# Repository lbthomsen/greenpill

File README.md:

# greenpill
STM32 Green Pill

https://stm32world.com/wiki/Green_Pill

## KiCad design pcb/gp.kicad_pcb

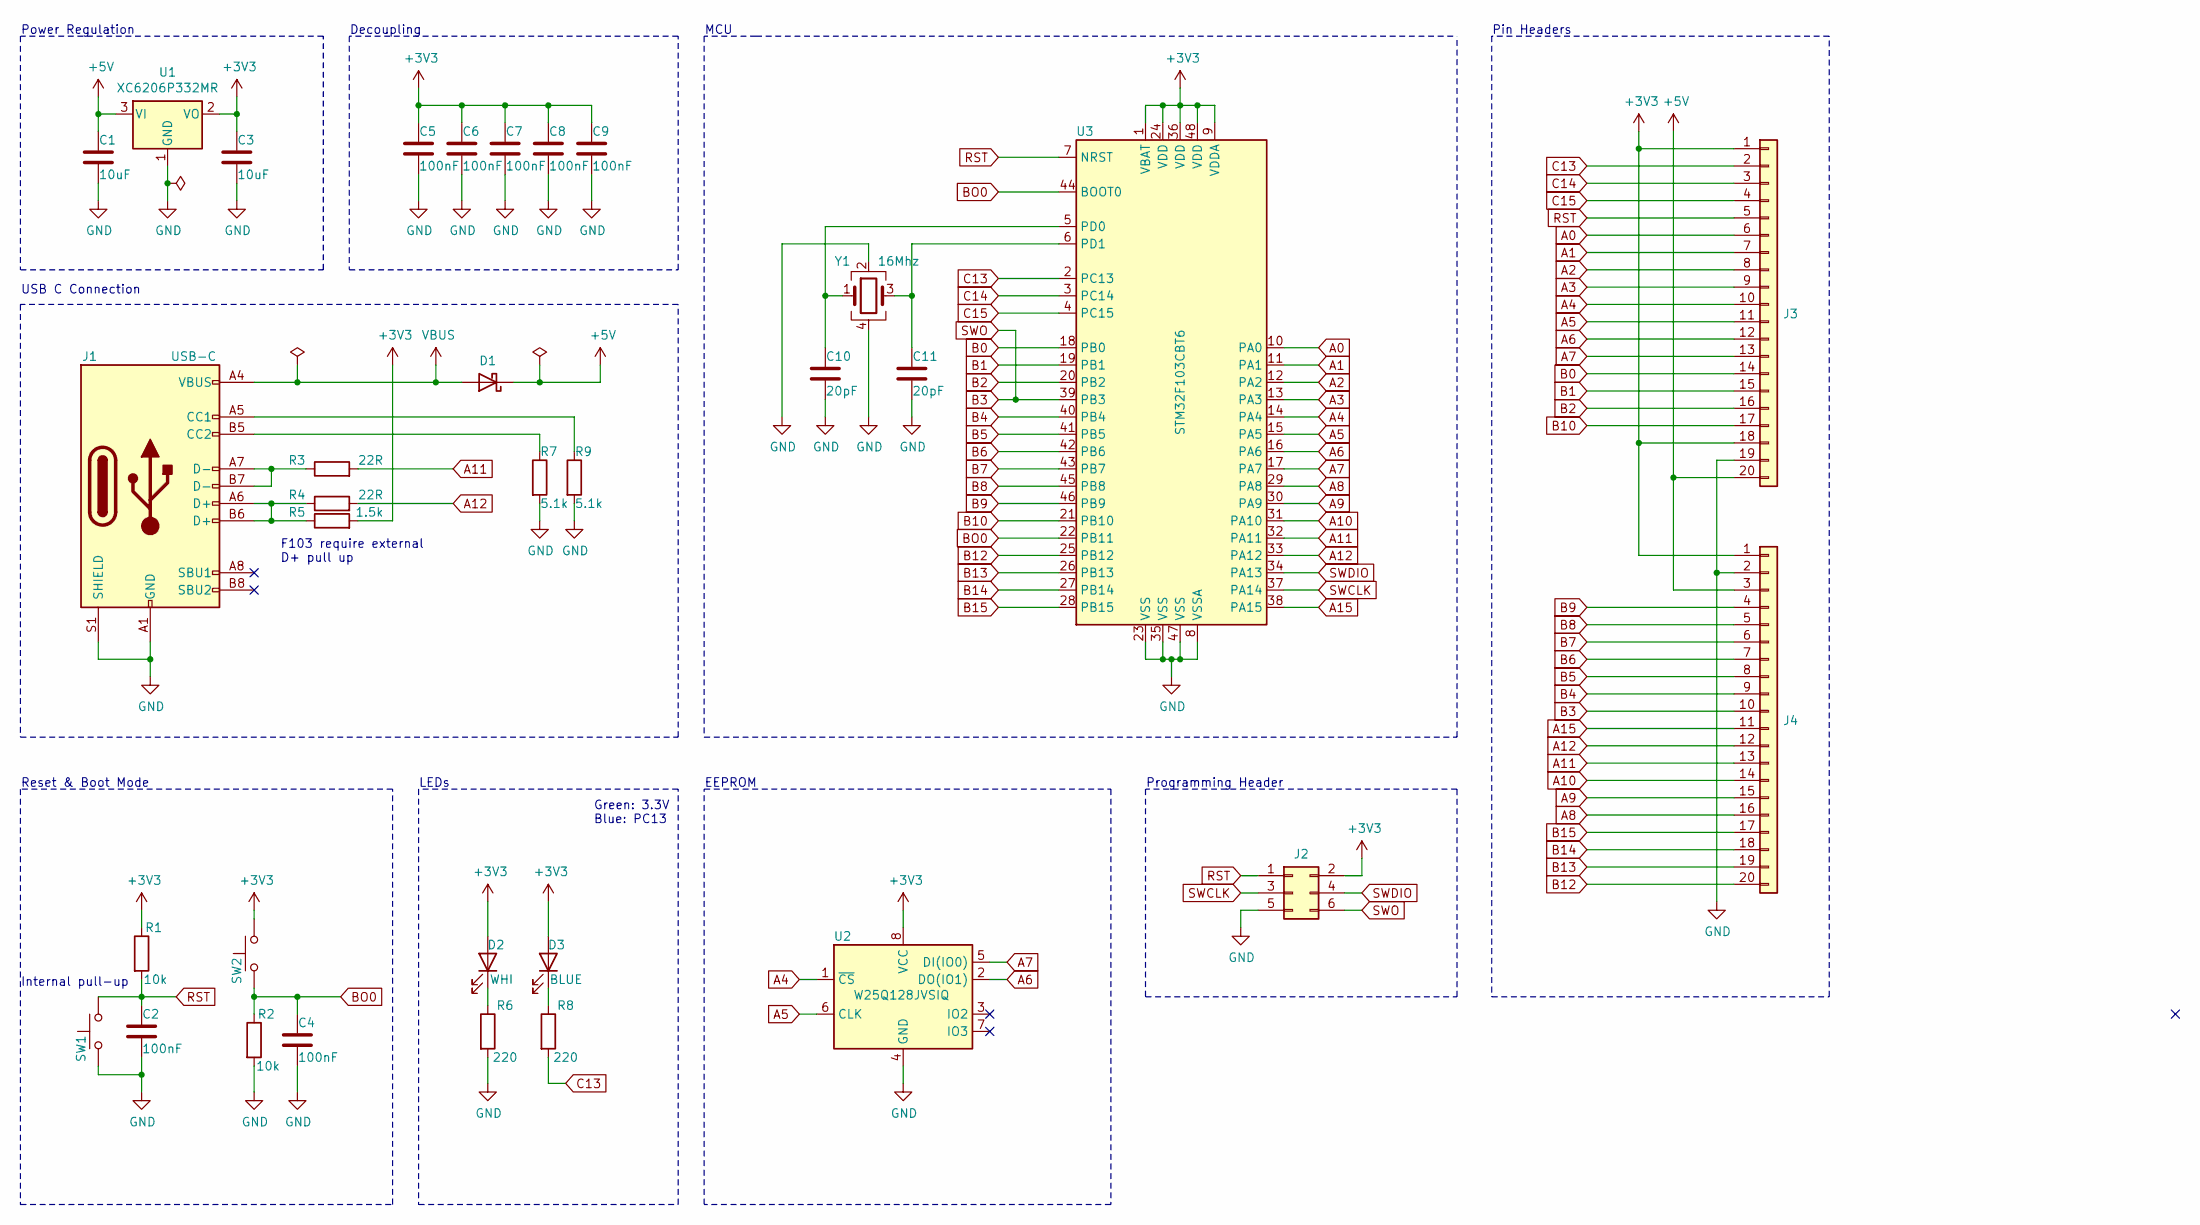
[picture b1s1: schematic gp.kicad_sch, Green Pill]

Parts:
C1, C3: 10uF; C_0603_1608Metric; LCSC C19702
C2, C4, C5, C6, C7, C8, C9: 100nF; C_0402_1005Metric; LCSC C1525
C10, C11: 20pF; C_0402_1005Metric; LCSC C1554
D1: D_SOD-123; LCSC C8598
D2: WHI; LED_0603_1608Metric; LCSC C2290
D3: BLUE; LED_0603_1608Metric; LCSC C2288
J1: USB-C; USB_C_Receptacle_HRO_TYPE-C-31-M-12; LCSC C165948
J2: PinHeader_2x03_P2.54mm_Horizontal
J3, J4: PinHeader_1x20_P2.54mm_Vertical
R1, R2: 10k; R_0402_1005Metric; LCSC C25744
R3, R4: 22R; R_0402_1005Metric; LCSC C25092
R5: 1.5k; R_0402_1005Metric; LCSC C25867
R6, R8: 220; R_0402_1005Metric; LCSC C25091
R7, R9: 5.1k; R_0402_1005Metric; LCSC C25905
SW1, SW2: TS-1088R-02526; LCSC C455281
U1: XC6206P332MR; SOT-23; LCSC C5446
U2: W25Q128JVSIQ; SOIC-8_5.3x5.3mm_P1.27mm; LCSC C97521
U3: STM32F103CBT6; LQFP-48_7x7mm_P0.5mm; LCSC C8304
Y1: 16Mhz; Crystal_SMD_3225-4Pin_3.2x2.5mm; LCSC C13738

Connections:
+3V3: C3.1, C5.1, C6.1, C7.1, C8.1, C9.1, D2.2 (A), D3.2 (A), J2.2, J3.1, J3.18, J4.1, R1.1, R5.2, SW2.2, U1.2 (VO), U2.8 (VCC), U3.1 (VBAT), U3.9 (VDDA), U3.24 (VDD), U3.36 (VDD), U3.48 (VDD)
+5V: C1.1, D1.1 (K), J3.20, J4.3, U1.3 (VI)
A0: J3.6, U3.10 (PA0)
A1: J3.7, U3.11 (PA1)
A2: J3.8, U3.12 (PA2)
A3: J3.9, U3.13 (PA3)
A4: J3.10, U2.1 (~CS), U3.14 (PA4)
A5: J3.11, U2.6 (CLK), U3.15 (PA5)
A6: J3.12, U2.2 (DO(IO1)), U3.16 (PA6)
A7: J3.13, U2.5 (DI(IO0)), U3.17 (PA7)
A8: J4.16, U3.29 (PA8)
A9: J4.15, U3.30 (PA9)
A10: J4.14, U3.31 (PA10)
A11: J4.13, R3.2, U3.32 (PA11)
A12: J4.12, R4.2, U3.33 (PA12)
A15: J4.11, U3.38 (PA15)
B0: J3.14, U3.18 (PB0)
B1: J3.15, U3.19 (PB1)
B2: J3.16, U3.20 (PB2)
B3: J2.6, J4.10, U3.39 (PB3)
B4: J4.9, U3.40 (PB4)
B5: J4.8, U3.41 (PB5)
B6: J4.7, U3.42 (PB6)
B7: J4.6, U3.43 (PB7)
B8: J4.5, U3.45 (PB8)
B9: J4.4, U3.46 (PB9)
B10: J3.17, U3.21 (PB10)
B12: J4.20, U3.25 (PB12)
B13: J4.19, U3.26 (PB13)
B14: J4.18, U3.27 (PB14)
B15: J4.17, U3.28 (PB15)
BO0: C4.1, R2.1, SW2.1, U3.22 (PB11), U3.44 (BOOT0)
C13: J3.2, R8.2, U3.2 (PC13)
C14: J3.3, U3.3 (PC14)
C15: J3.4, U3.4 (PC15)
GND: C1.2, C2.2, C3.2, C4.2, C5.2, C6.2, C7.2, C8.2, C9.2, C10.2, C11.2, J1.A1 (GND), J1.A12 (GND), J1.B1 (GND), J1.B12 (GND), J1.S1 (SHIELD), J2.5, J3.19, J4.2, R2.2, R6.2, R7.2, R9.2, SW1.1, U1.1 (GND), U2.4 (GND), U3.8 (VSSA), U3.23 (VSS), U3.35 (VSS), U3.47 (VSS), Y1.2, Y1.4
unnamed: D2.1 (K), R6.1
unnamed: D3.1 (K), R8.1
unnamed: J1.A5 (CC1), R9.1
unnamed: J1.B5 (CC2), R7.1
unnamed: J1.A6 (D+), J1.B6 (D+), R4.1, R5.1
unnamed: J1.A7 (D-), J1.B7 (D-), R3.1
unnamed: C10.1, U3.5 (PD0), Y1.1
unnamed: C11.1, U3.6 (PD1), Y1.3
RST: C2.1, J2.1, J3.5, R1.2, SW1.2, U3.7 (NRST)
SWCLK: J2.3, U3.37 (PA14)
SWDIO: J2.4, U3.34 (PA13)
VBUS: D1.2 (A), J1.A4 (VBUS), J1.A9 (VBUS), J1.B4 (VBUS), J1.B9 (VBUS)

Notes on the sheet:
Decoupling
Green: 3.3V Blue: PC13
MCU
Reset & Boot Mode
USB C Connection
Internal pull-up
Power Regulation
Pin Headers
F103 require external D+ pull up
Programming Header
LEDs
EEPROM

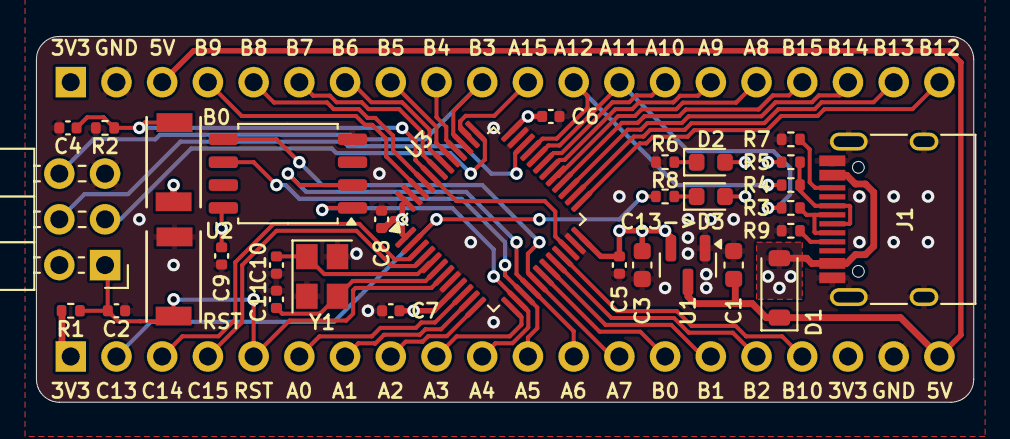
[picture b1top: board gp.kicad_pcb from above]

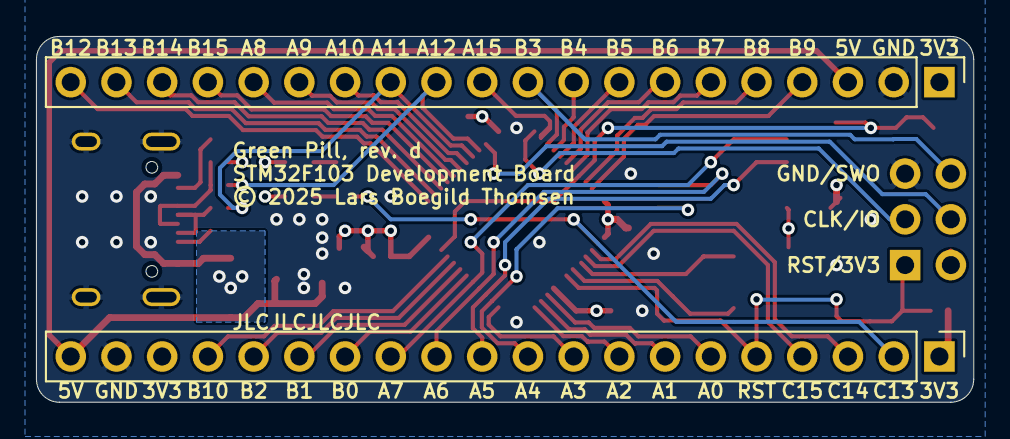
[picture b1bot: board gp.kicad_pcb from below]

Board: 4 copper layers, 52.1 x 20.3 mm, 33 parts (2 on the bottom side), 48 nets.

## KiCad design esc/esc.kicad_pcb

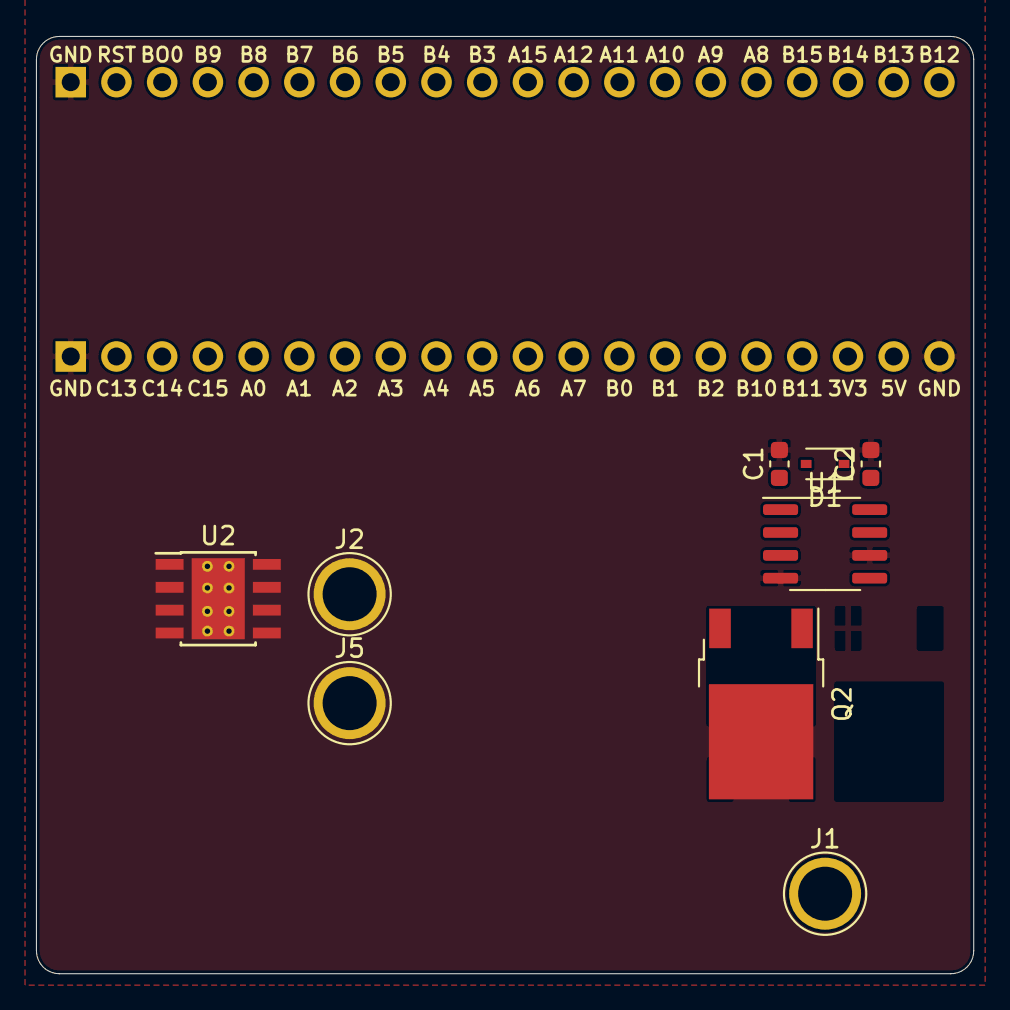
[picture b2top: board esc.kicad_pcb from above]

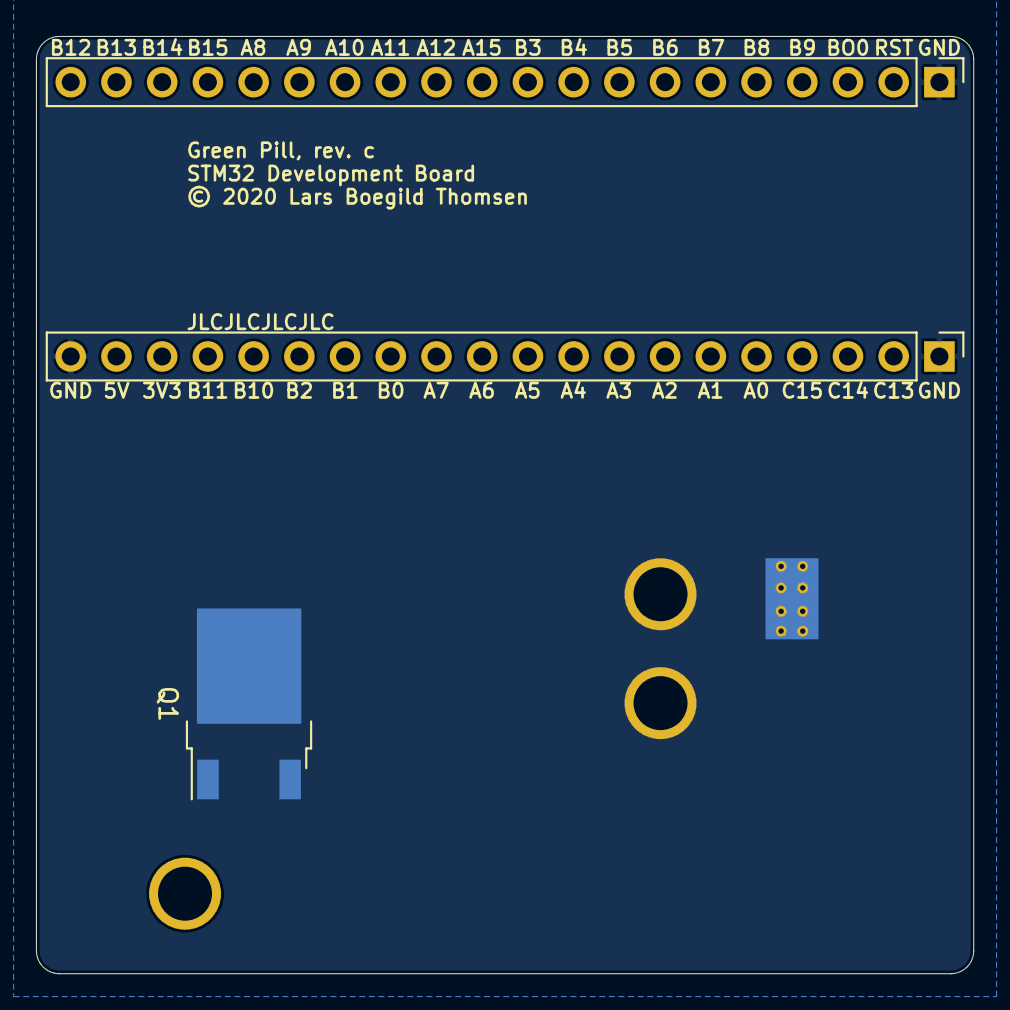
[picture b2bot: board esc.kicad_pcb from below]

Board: 2 copper layers, 52.1 x 52.1 mm, 12 parts (3 on the bottom side), 6 nets, no tracks yet.

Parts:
C1, C2: C; C_0603_1608Metric
D1: D_SOD-323
J1, J2, J5: TestPoint_Plated_Hole_D3.0mm
J3, J4: PinHeader_1x20_P2.54mm_Vertical
Q1, Q2: NCEP60T12AK; TO-252-2
U1: IR2101; SOIC-8_3.9x4.9mm_P1.27mm
U2: TPS5430DDA; TI_SO-PowerPAD-8_ThermalVias

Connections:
+3V3: C1.1, D1.2, J3.18, U1.1
A: J1.1, Q1.3, Q2.2
DAH: Q1.1, U1.7
DAL: Q2.1, U1.5
GND: C1.2, C2.2, J3.1, J3.20, J4.1, J5.1, Q2.3, U1.4, U1.6
VDC: C2.1, D1.1, Q1.2, U1.8

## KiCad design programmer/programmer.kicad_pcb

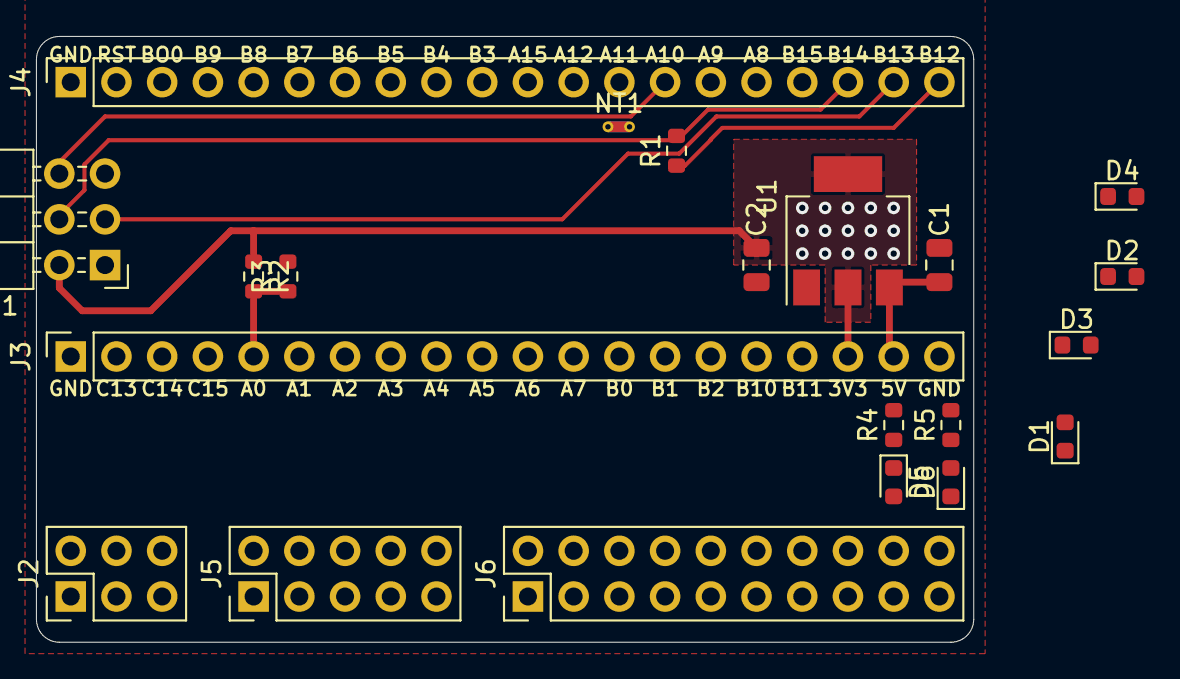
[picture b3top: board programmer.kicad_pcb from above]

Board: 2 copper layers, 52.1 x 33.7 mm, 21 parts (0 on the bottom side), 12 nets.

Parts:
C1, C2: 10uF; C_0805_2012Metric
D1: YL; LED_0603_1608Metric
D2: GR; LED_0603_1608Metric
D3, D6: BL; LED_0603_1608Metric
D4, D5: RD; LED_0603_1608Metric
J1: PinHeader_2x03_P2.54mm_Horizontal
J2: PinHeader_2x03_P2.54mm_Vertical
J3, J4: PinSocket_1x20_P2.54mm_Vertical
J5: PinHeader_2x05_P2.54mm_Vertical
J6: PinHeader_2x10_P2.54mm_Vertical
NT1: NetTie-2_THT_Pad0.3mm
R1: 100; R_0603_1608Metric
R2, R3: 4.7; R_0603_1608Metric
R4, R5: 470; R_0603_1608Metric
U1: AMS1117-3.3; SOT-223-3_TabPin2

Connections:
+3V3: C2.1, D5.2, J1.2, J2.2, J3.18, R2.1, U1.2
+5V: C1.1, J3.19, U1.3
A0: J3.5, R2.2, R3.1
A9: J4.15, R4.2, R5.2
A10: J4.14, NT1.2
B12: J4.20, R1.1
B13: J1.3, J2.3, J4.19
B14: J1.4, J2.4, J4.18, R1.2
GND: C1.2, C2.2, D6.1, J1.5, J2.5, J3.1, J3.20, J4.1, R3.2, U1.1
unnamed: D5.1, R4.1
unnamed: D6.2, R5.1
T_SWO: J1.6, J2.6, NT1.1

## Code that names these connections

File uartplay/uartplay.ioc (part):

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Mcu.Name=STM32F103C(8-B)Tx
Mcu.Package=LQFP48
Mcu.UserName=STM32F103CBTx
PA0-WKUP.GPIOParameters=GPIO_Label
PA0-WKUP.GPIO_Label=DEBUG
PA0-WKUP.Signal=GPIO_Output
PA10.Mode=Asynchronous
PA10.Signal=USART1_RX
PA13.Mode=Serial_Wire
PA13.Signal=SYS_JTMS-SWDIO
PA14.Mode=Serial_Wire
PA14.Signal=SYS_JTCK-SWCLK
PA2.Mode=Asynchronous
PA2.Signal=USART2_TX
PA3.Mode=Asynchronous
PA3.Signal=USART2_RX
PA9.Mode=Asynchronous
PA9.Signal=USART1_TX
PB10.Mode=Asynchronous
PB10.Signal=USART3_TX
PB11.Mode=Asynchronous
PB11.Signal=USART3_RX
PC13-TAMPER-RTC.GPIOParameters=PinState,GPIO_PuPd,GPIO_Label,GPIO_ModeDefaultOutputPP
PC13-TAMPER-RTC.GPIO_Label=LED
PC13-TAMPER-RTC.GPIO_ModeDefaultOutputPP=GPIO_MODE_OUTPUT_OD
PC13-TAMPER-RTC.GPIO_PuPd=GPIO_NOPULL
PC13-TAMPER-RTC.PinState=GPIO_PIN_RESET
PC13-TAMPER-RTC.Signal=GPIO_Output
PD0-OSC_IN.Mode=HSE-External-Oscillator
PD0-OSC_IN.Signal=RCC_OSC_IN
PD1-OSC_OUT.Mode=HSE-External-Oscillator
PD1-OSC_OUT.Signal=RCC_OSC_OUT
RCC.SYSCLKFreq_VALUE=72000000
RCC.SYSCLKSource=RCC_SYSCLKSOURCE_PLLCLK
board=custom

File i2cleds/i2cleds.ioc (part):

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Mcu.Name=STM32F103C(8-B)Tx
Mcu.Package=LQFP48
Mcu.UserName=STM32F103C8Tx
PA11.Mode=Device
PA11.Signal=USB_DM
PA12.Mode=Device
PA12.Signal=USB_DP
PA13.Mode=Trace_Asynchronous_SW
PA13.Signal=SYS_JTMS-SWDIO
PA14.Mode=Trace_Asynchronous_SW
PA14.Signal=SYS_JTCK-SWCLK
PA4.Signal=GPIO_Output
PB3.Mode=Trace_Asynchronous_SW
PB3.Signal=SYS_JTDO-TRACESWO
PB5.Signal=GPIO_Output
PB6.Mode=I2C
PB6.Signal=I2C1_SCL
PB7.Mode=I2C
PB7.Signal=I2C1_SDA
PC13-TAMPER-RTC.Signal=GPIO_Output
PD0-OSC_IN.Mode=HSE-External-Oscillator
PD0-OSC_IN.Signal=RCC_OSC_IN
PD1-OSC_OUT.Mode=HSE-External-Oscillator
PD1-OSC_OUT.Signal=RCC_OSC_OUT
RCC.SYSCLKFreq_VALUE=72000000
RCC.SYSCLKSource=RCC_SYSCLKSOURCE_PLLCLK
board=custom

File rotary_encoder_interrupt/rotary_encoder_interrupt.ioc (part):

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Mcu.Name=STM32F103C(8-B)Tx
Mcu.Package=LQFP48
Mcu.UserName=STM32F103CBTx
PA10.Mode=Asynchronous
PA10.Signal=USART1_RX
PA13.Mode=Serial_Wire
PA13.Signal=SYS_JTMS-SWDIO
PA14.Mode=Serial_Wire
PA14.Signal=SYS_JTCK-SWCLK
PA5.GPIOParameters=GPIO_Label,GPIO_ModeDefaultEXTI
PA5.GPIO_Label=ROT_C
PA5.GPIO_ModeDefaultEXTI=GPIO_MODE_IT_FALLING
PA5.Signal=GPXTI5
PA6.GPIOParameters=GPIO_Label,GPIO_ModeDefaultEXTI
PA6.GPIO_Label=ROT_B
PA6.GPIO_ModeDefaultEXTI=GPIO_MODE_IT_RISING_FALLING
PA6.Signal=GPXTI6
PA7.GPIOParameters=GPIO_Label,GPIO_ModeDefaultEXTI
PA7.GPIO_Label=ROT_A
PA7.GPIO_ModeDefaultEXTI=GPIO_MODE_IT_RISING_FALLING
PA7.Signal=GPXTI7
PA9.Mode=Asynchronous
PA9.Signal=USART1_TX
PB9.GPIOParameters=GPIO_Label
PB9.GPIO_Label=LED
PB9.Signal=S_TIM4_CH4
PD0-OSC_IN.Mode=HSE-External-Oscillator
PD0-OSC_IN.Signal=RCC_OSC_IN
PD1-OSC_OUT.Mode=HSE-External-Oscillator
PD1-OSC_OUT.Signal=RCC_OSC_OUT
RCC.SYSCLKFreq_VALUE=48000000
RCC.SYSCLKSource=RCC_SYSCLKSOURCE_PLLCLK
board=custom

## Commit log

2020-07-24 3 different blink approaches - delay, tick triggered and timer.
2020-07-25 Hmmmm
2020-07-26 Hmmm
2020-07-27 Added PCB
2020-07-28 Added i2c GPIO LED Driver Example
2020-07-29 Playing with gpio expander
2020-10-11 Rev c almost done
2020-10-11 Added rev c production files
2020-10-12 Added headers
2020-11-02 Removed Debug folders
2020-11-03 Minor tweaks
2020-11-03 Updated pcb
2020-11-27 Changed buttons
2020-11-29 Rev c ready to order - production files gp_c verified.
2020-12-19 Order rev c
2020-12-19 stm32l version
2020-12-20 New export
2021-02-08 Added blink4
2021-02-08 Added README
2021-02-08 Added more links
2021-02-08 Fixed link
2021-03-26 Tweaks for rev c
2021-04-15 Added pdf
2021-04-16 Bumped to rev .d (check out rev_c tag for last prod)
2021-04-16 Minor tweak
2021-04-18 Minor tweaks - only cosmetic
2021-06-03 Added gd32f103 version of blink
2021-06-19 Update main.c
    Better and simpler timing
2021-06-19 Update main.c
    Fixed stupid mistake
2021-07-26 A few more comments
2021-08-25 Readded pull down on boot0
2021-08-26 Checking if I can add w25qxxx
2022-08-19 MIDI2 working
2022-08-19 midi2 works as hid
2022-08-20 midi2 working!
2022-08-20 midi2 working perfectly
2024-03-13 Tweaking
2025-03-09 Reorganised
2025-03-09 Minor rev. d changes
2025-03-10 More fine tuning of PCB
2025-03-11 Tweaks
2025-05-22 Just updated kicad version

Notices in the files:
esc/esc.kicad_pcb:
© 2020 Lars Boegild Thomsen
pcb/gp.kicad_pcb:
© 2025 Lars Boegild Thomsen
